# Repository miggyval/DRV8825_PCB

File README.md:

This is a repository for the DRV8825 PCB KiCAD project by Miguel Valencia

[Link to BOM](https://html-preview.github.io/?url=https://github.com/miggyval/DRV8825_PCB/blob/main/bom/ibom.html)

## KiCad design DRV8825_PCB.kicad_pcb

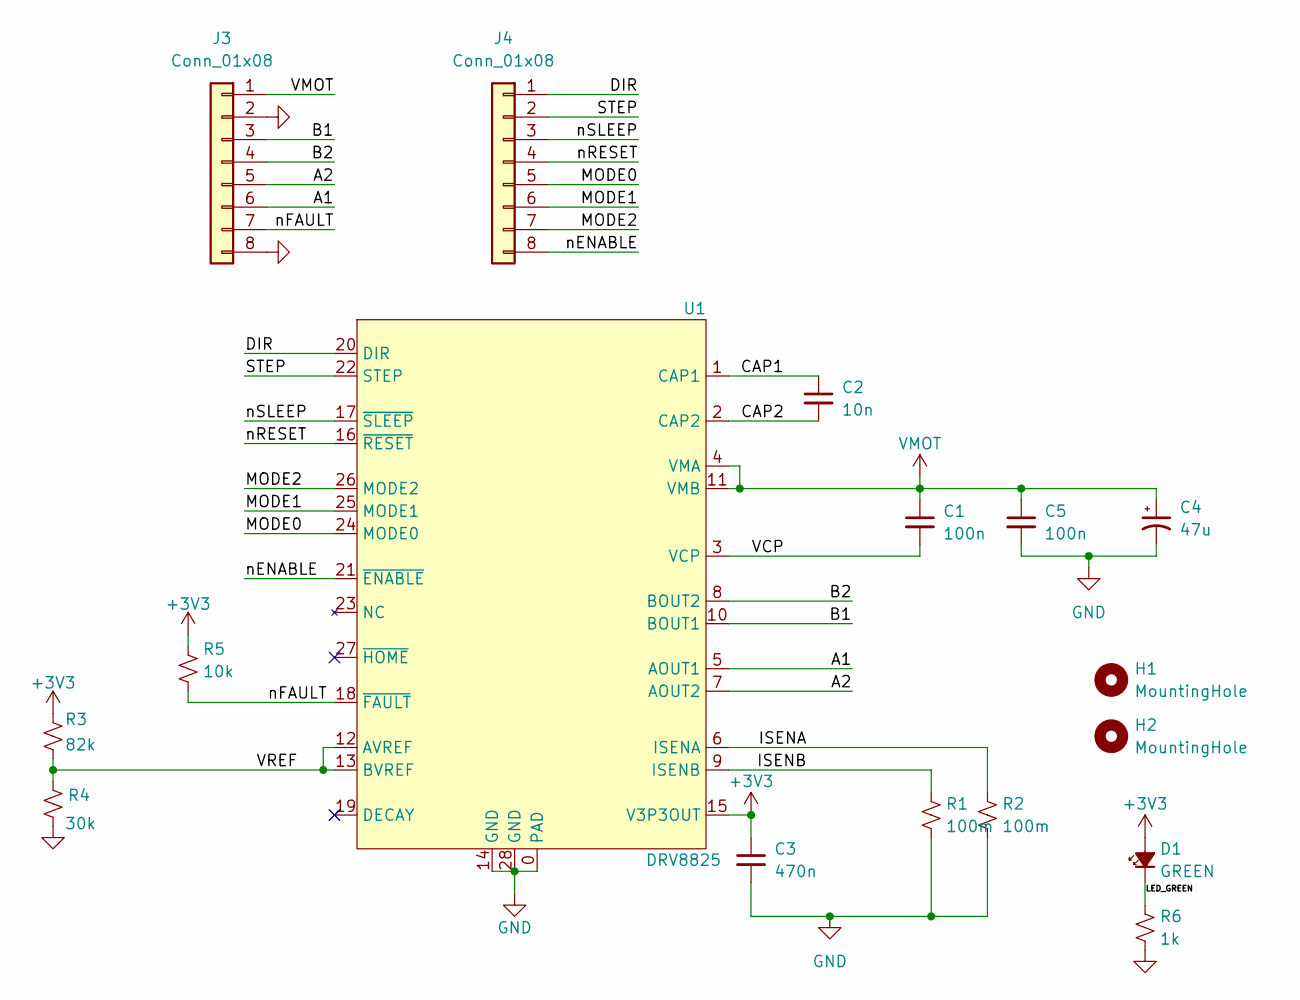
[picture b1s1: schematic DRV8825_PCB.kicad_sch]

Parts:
C1, C5: 100n; C_0603_1608Metric
C2: 10n; C_0603_1608Metric
C3: 470n; C_0603_1608Metric
C4: 47u; CP_Elec_6.3x5.9
D1: GREEN; LED_0603_1608Metric
H1, H2: MountingHole; MountingHole_2.2mm_M2
J3, J4: Conn_01x08; PinHeader_1x08_P2.54mm_Vertical
R1, R2: 100m; R_1206_3216Metric
R3: 82k; R_0603_1608Metric; DigiKey Description RES 78.7 OHMS 0.1% 0.4W 1206
R4: 30k; R_0603_1608Metric; DigiKey Description RES SMD 30K OHM 0.1% 1/10W 0805
R5: 10k; R_0603_1608Metric; DigiKey Description RES 78.7 OHMS 0.1% 0.4W 1206
R6: 1k; R_0603_1608Metric
U1: DRV8825; IC_TPS61196PWPRQ1

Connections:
+3V3: C3.1, D1.2 (A), R3.1, R5.1, U1.15 (V3P3OUT)
/A1: J3.6, U1.5 (AOUT1)
/A2: J3.5, U1.7 (AOUT2)
/B1: J3.3, U1.10 (BOUT1)
/B2: J3.4, U1.8 (BOUT2)
/CAP1: C2.1, U1.1 (CAP1)
/CAP2: C2.2, U1.2 (CAP2)
/DIR: J4.1, U1.20 (DIR)
/ISENA: R2.2, U1.6 (ISENA)
/ISENB: R1.2, U1.9 (ISENB)
/LED_GREEN: D1.1 (K), R6.2
/MODE0: J4.5, U1.24 (MODE0)
/MODE1: J4.6, U1.25 (MODE1)
/MODE2: J4.7, U1.26 (MODE2)
/STEP: J4.2, U1.22 (STEP)
/VCP: C1.2, U1.3 (VCP)
/VREF: R3.2, R4.1, U1.12 (AVREF), U1.13 (BVREF)
/nENABLE: J4.8, U1.21 (~ENABLE)
/nFAULT: J3.7, R5.2, U1.18 (~FAULT)
/nRESET: J4.4, U1.16 (~RESET)
/nSLEEP: J4.3, U1.17 (~SLEEP)
GND: C3.2, C4.2, C5.2, J3.2, J3.8, R1.1, R2.1, R4.2, R6.1, U1.0 (PAD), U1.14 (GND), U1.28 (GND)
VMOT: C1.1, C4.1, C5.1, J3.1, U1.4 (VMA), U1.11 (VMB)

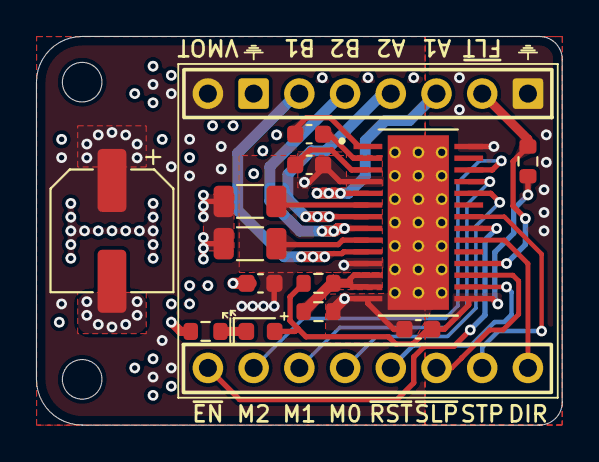
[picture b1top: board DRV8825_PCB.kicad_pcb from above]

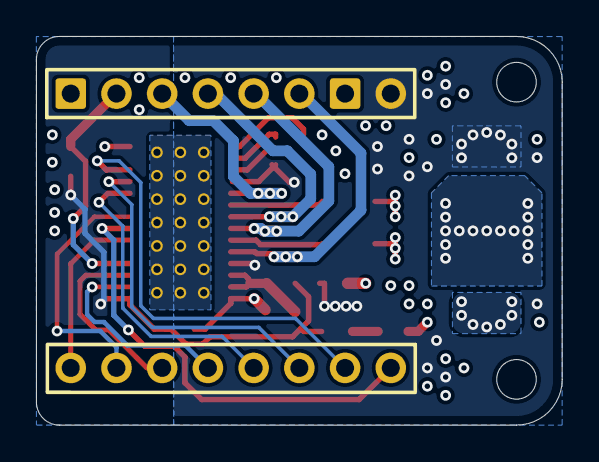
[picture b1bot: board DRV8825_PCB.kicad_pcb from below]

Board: 4 copper layers, 29.2 x 21.6 mm, 17 parts (2 on the bottom side), 23 nets.

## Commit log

2024-09-30 First commit!
